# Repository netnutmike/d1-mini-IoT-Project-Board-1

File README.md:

# d1-mini-IoT-Project-Board-1
This is a board designed for the D1 Mini with lots of io for IoT projects

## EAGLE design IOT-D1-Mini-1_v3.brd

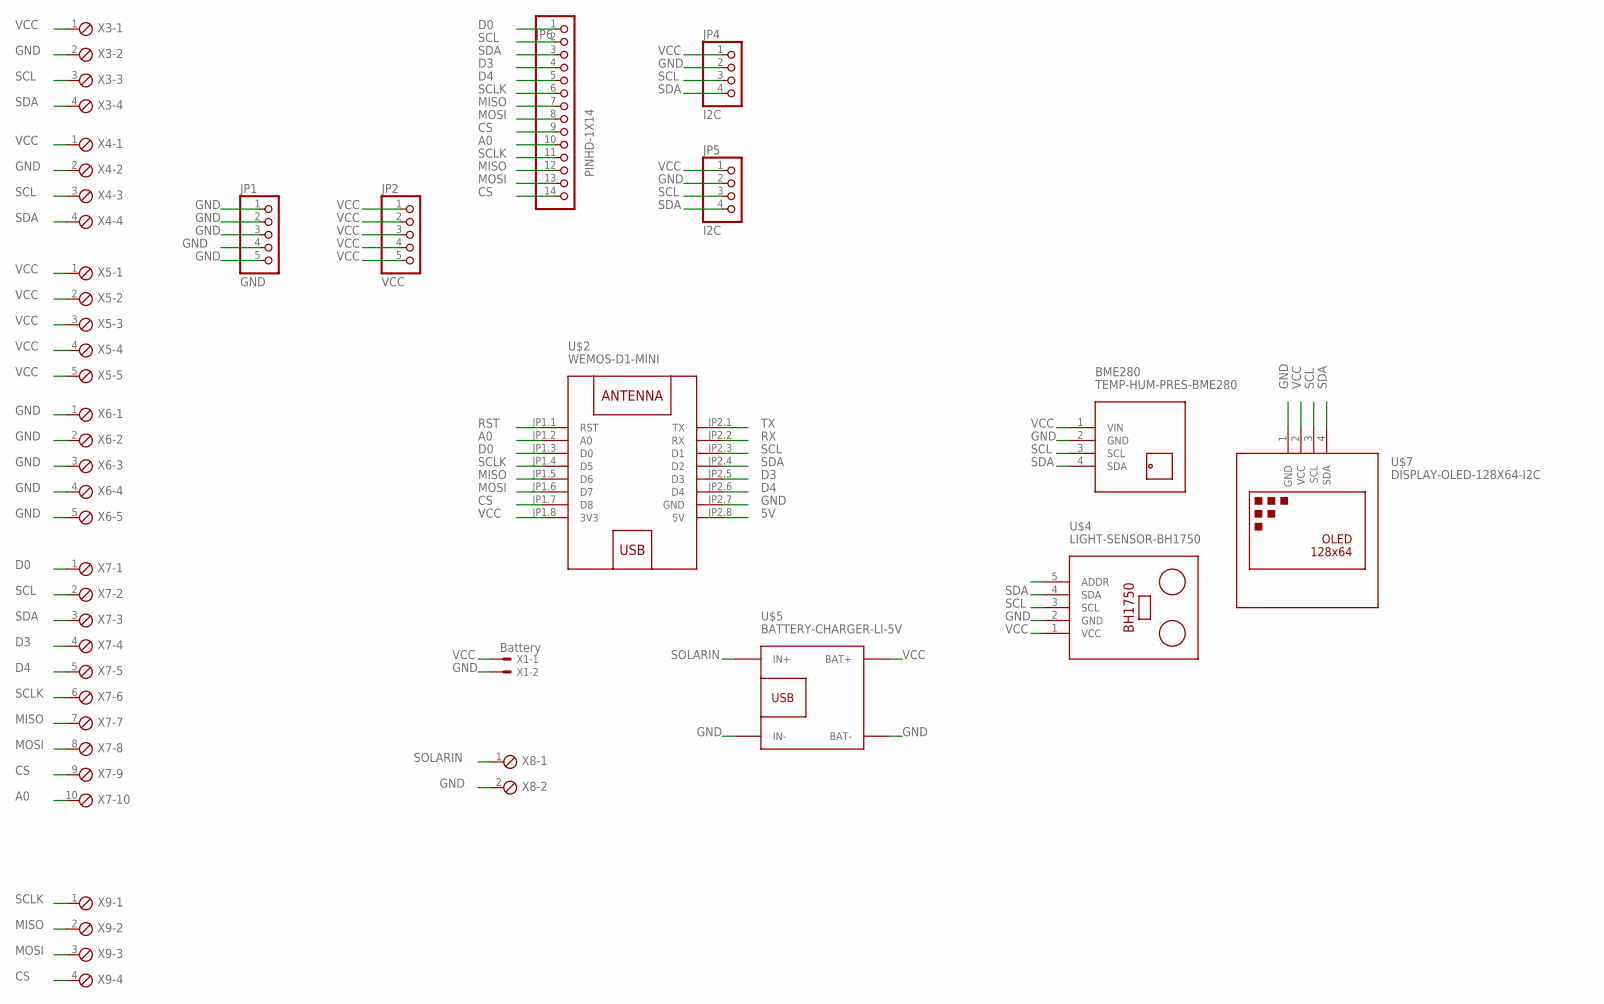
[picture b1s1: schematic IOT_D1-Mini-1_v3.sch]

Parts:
BME280: TEMP-HUM-PRES-BME280
JP1: GND; 1X05
JP2: VCC; 1X05
JP4, JP5: I2C; 1X04
JP6: PINHD-1X14; 1X14
U$2: WEMOS-D1-MINI
U$4: LIGHT-SENSOR-BH1750
U$5: BATTERY-CHARGER-LI-5V
U$7: DISPLAY-OLED-128X64-I2C
X1: Battery; 53047-02
X3, X4, X9: MPT4; 4POL254
X5, X6: MPT5; 5POL254
X7: MPT10; 10POL254
X8: MPT2; 2POL254

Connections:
5V: U$2.JP2.8 (5V)
A0: JP6.10, U$2.JP1.2 (A0), X7.10
CS: JP6.9, JP6.14, U$2.JP1.7 (D8), X7.9, X9.4
D0: JP6.1, U$2.JP1.3 (D0), X7.1
D3: JP6.4, U$2.JP2.5 (D3), X7.4
D4: JP6.5, U$2.JP2.6 (D4), X7.5
GND: BME280.2 (GND), JP1.1, JP1.2, JP1.3, JP1.4, JP1.5, JP4.2, JP5.2, U$2.JP2.7 (GND), U$4.2 (GND), U$5.BAT-, U$5.IN-, U$7.1 (GND), X1.2, X3.2, X4.2, X6.1, X6.2, X6.3, X6.4, X6.5, X8.2
MISO: JP6.7, JP6.12, U$2.JP1.5 (D6), X7.7, X9.2
MOSI: JP6.8, JP6.13, U$2.JP1.6 (D7), X7.8, X9.3
RST: U$2.JP1.1 (RST)
RX: U$2.JP2.2 (RX)
SCL: BME280.3 (SCL), JP4.3, JP5.3, JP6.2, U$2.JP2.3 (D1), U$4.3 (SCL), U$7.3 (SCL), X3.3, X4.3, X7.2
SCLK: JP6.6, JP6.11, U$2.JP1.4 (D5), X7.6, X9.1
SDA: BME280.4 (SDA), JP4.4, JP5.4, JP6.3, U$2.JP2.4 (D2), U$4.4 (SDA), U$7.4 (SDA), X3.4, X4.4, X7.3
SOLARIN: U$5.IN+, X8.1
TX: U$2.JP2.1 (TX)
VCC: BME280.1 (VIN), JP2.1, JP2.2, JP2.3, JP2.4, JP2.5, JP4.1, JP5.1, U$2.JP1.8 (3V3), U$4.1 (VCC), U$5.BAT+, U$7.2 (VCC), X1.1, X3.1, X4.1, X5.1, X5.2, X5.3, X5.4, X5.5

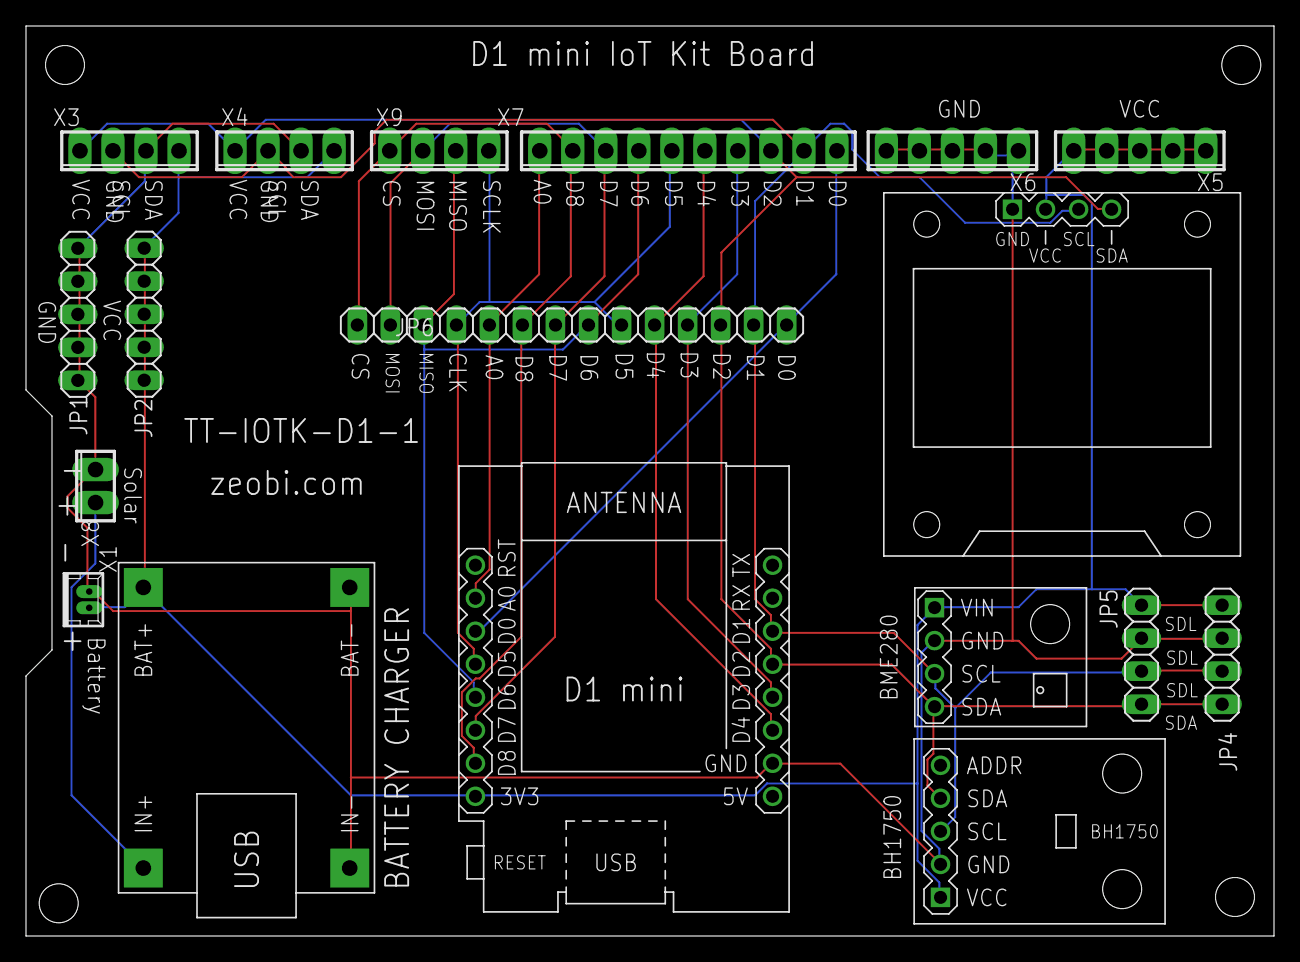
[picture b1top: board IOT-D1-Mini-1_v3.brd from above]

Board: 2 copper layers, 96.0 x 70.0 mm, 18 parts (0 on the bottom side), 13 nets.

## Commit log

2021-01-22 initial load

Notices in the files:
parts and their libraries:
diy-modules: Released under the Creative Commons Attribution 4.0 International License: http://creativecommons.org/licenses/by/4.0
